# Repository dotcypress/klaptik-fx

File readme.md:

# klaptik-fx-app

## License

Licensed under either of

- Apache License, Version 2.0 ([LICENSE-APACHE](LICENSE-APACHE) or
  http://www.apache.org/licenses/LICENSE-2.0)
- MIT license ([LICENSE-MIT](LICENSE-MIT) or http://opensource.org/licenses/MIT)

at your option.

### Contribution

Unless you explicitly state otherwise, any contribution intentionally submitted
for inclusion in the work by you, as defined in the Apache-2.0 license, shall be
dual licensed as above, without any additional terms or conditions.

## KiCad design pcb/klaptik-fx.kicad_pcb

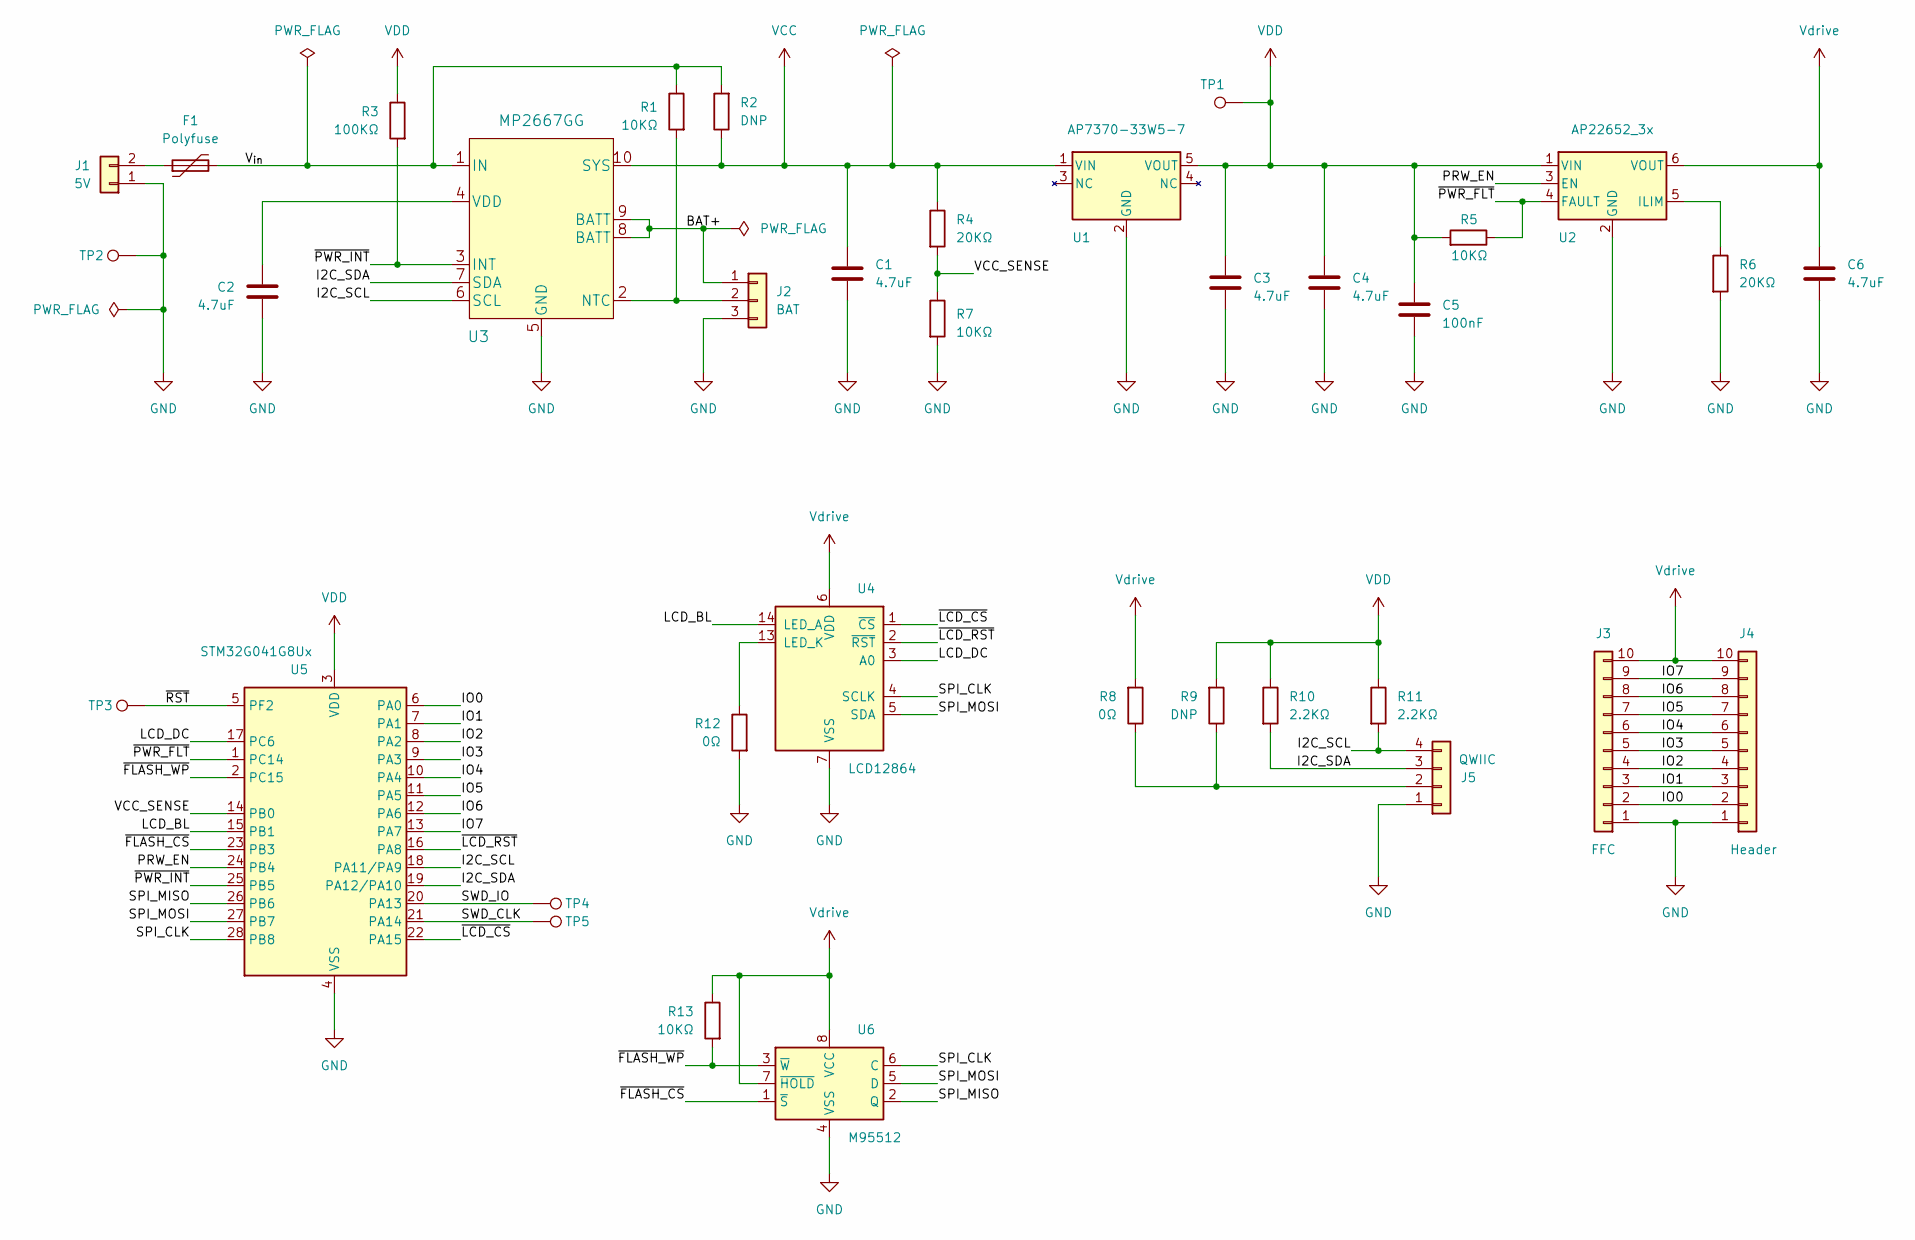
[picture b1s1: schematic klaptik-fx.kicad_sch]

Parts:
C1, C2, C3, C4, C6: 4.7uF; C_0402_1005Metric
C5: 100nF; C_0402_1005Metric
F1: Polyfuse; Fuse_0402_1005Metric
J1: 5V; PinHeader_1x02_P2.54mm_Vertical
J2: BAT; JST_SH_SM03B-SRSS-TB_1x03-1MP_P1.00mm_Horizontal
J3: FFC; Molex_54548-1071_1x10-1MP_P0.5mm_Horizontal
J4: Header; PinHeader_1x10_P1.27mm_Vertical
J5: QWIIC; JST_SH_SM04B-SRSS-TB_1x04-1MP_P1.00mm_Horizontal
R1, R5, R7, R13: 10KΩ; R_0402_1005Metric
R2, R9: DNP; R_0402_1005Metric
R3: 100KΩ; R_0402_1005Metric
R4, R6: 20KΩ; R_0402_1005Metric
R8, R12: 0Ω; R_0402_1005Metric
R10, R11: 2.2KΩ; R_0402_1005Metric
TP1: VDD; TestPoint_Pad_D1.0mm
TP2, TP3: GND; TestPoint_Pad_D1.0mm
TP4: SWD IO; TestPoint_Pad_D1.0mm
TP5: SWD CLK; TestPoint_Pad_D1.0mm
U1: AP7370-33W5-7; TSOT-23-5
U2: AP22652_3x; SOT-23-6
U3: MP2667GG; MP2667GG-xxxx-Z
U4: LCD12864; LCD_FPC_1x14_P0.80mm
U5: STM32G041G8Ux; QFN-28_4x4mm_P0.5mm
U6: M95512; TSSOP-8_4.4x3mm_P0.65mm

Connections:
/BAT+: J2.1, U3.8 (BATT), U3.9 (BATT)
/I2C_SCL: J5.4, R11.2, U3.6 (SCL), U5.18 (PA11/PA9)
/I2C_SDA: J5.3, R10.2, U3.7 (SDA), U5.19 (PA12/PA10)
/IO0: J3.2, J4.2, U5.6 (PA0)
/IO1: J3.3, J4.3, U5.7 (PA1)
/IO2: J3.4, J4.4, U5.8 (PA2)
/IO3: J3.5, J4.5, U5.9 (PA3)
/IO4: J3.6, J4.6, U5.10 (PA4)
/IO5: J3.7, J4.7, U5.11 (PA5)
/IO6: J3.8, J4.8, U5.12 (PA6)
/IO7: J3.9, J4.9, U5.13 (PA7)
/LCD_BL: U4.14 (LED_A), U5.15 (PB1)
/LCD_DC: U4.3 (A0), U5.17 (PC6)
/PRW_EN: U2.3 (EN), U5.24 (PB4)
/SPI_CLK: U4.4 (SCLK), U5.28 (PB8), U6.6 (C)
/SPI_MISO: U5.26 (PB6), U6.2 (Q)
/SPI_MOSI: U4.5 (SDA), U5.27 (PB7), U6.5 (D)
/SWD_CLK: TP5.1, U5.21 (PA14)
/SWD_IO: TP4.1, U5.20 (PA13)
/VCC_SENSE: R4.2, R7.1, U5.14 (PB0)
/V_{in}: F1.2, R1.1, R2.2, U3.1 (IN)
/~FLASH_CS: U5.23 (PB3), U6.1 (~S)
/~FLASH_WP: R13.2, U5.2 (PC15), U6.3 (~W)
/~LCD_CS: U4.1 (~CS), U5.22 (PA15)
/~LCD_RST: U4.2 (~RST), U5.16 (PA8)
/~PWR_FLT: R5.1, U2.4 (FAULT), U5.1 (PC14)
/~PWR_INT: R3.2, U3.3 (INT), U5.25 (PB5)
/~RST: TP3.1, U5.5 (PF2)
GND: C1.2, C2.2, C3.2, C4.2, C5.2, C6.2, J1.1, J2.3, J3.1, J4.1, J5.1, R6.2, R7.2, R12.2, TP2.1, U1.2 (GND), U2.2 (GND), U3.5 (GND), U4.7 (VSS), U5.4 (VSS), U6.4 (VSS)
unnamed: F1.1, J1.2
unnamed: J2.2, R1.2, U3.2 (NTC)
unnamed: J5.2, R8.1, R9.1
unnamed: R6.1, U2.5 (ILIM)
unnamed: C2.1, U3.4 (VDD)
unnamed: R12.1, U4.13 (LED_K)
VCC: C1.1, R2.1, R4.1, U1.1 (VIN), U3.10 (SYS)
VDD: C3.1, C4.1, C5.1, R3.1, R5.2, R9.2, R10.1, R11.1, TP1.1, U1.5 (VOUT), U2.1 (VIN), U5.3 (VDD)
Vdrive: C6.1, J3.10, J4.10, R8.2, R13.1, U2.6 (VOUT), U4.6 (VDD), U6.7 (~HOLD), U6.8 (VCC)

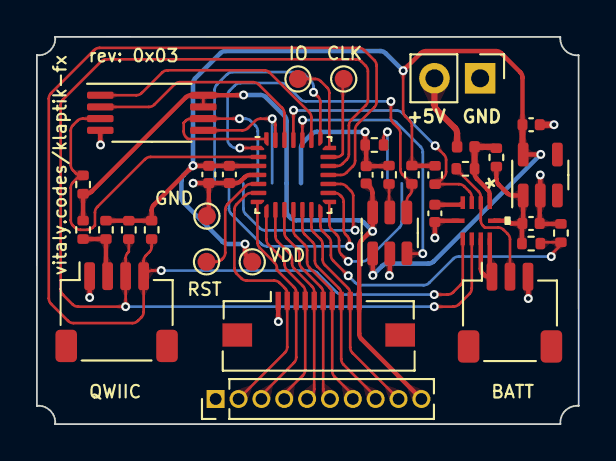
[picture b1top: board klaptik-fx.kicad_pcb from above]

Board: 4 copper layers, 30.1 x 21.5 mm, 36 parts (1 on the bottom side), 38 nets.

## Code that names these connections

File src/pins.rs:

use crate::hal::gpio::{gpioa::*, gpiob::*, gpioc::*};
use hal::gpio::*;
use hal::gpio::{DefaultMode, OpenDrain, Output, PushPull};
use hal::prelude::*;
use hal::rcc::Rcc;
use hal::stm32::*;

// SWD
pub type SwdIo = PA13<DefaultMode>;
pub type SwdClk = PA14<DefaultMode>;

// Qwiic I2C
pub type I2cClk = PA11<Output<OpenDrain>>;
pub type I2cSda = PA12<Output<OpenDrain>>;

// SPI
pub type SpiClk = PB8<DefaultMode>;
pub type SpiMiso = PB6<DefaultMode>;
pub type SpiMosi = PB7<DefaultMode>;

// Display
pub type LcdDC = PC6<Output<PushPull>>;
pub type LcdCS = PA15<Output<PushPull>>;
pub type LcdReset = PA8<Output<PushPull>>;
pub type LcdBacklight = PB1<DefaultMode>;

// EEPROM
pub type EepromCS = PB3<Output<PushPull>>;
pub type EepromWP = PC15<Output<PushPull>>;

// Power
pub type PowerEn = PB4<Output<PushPull>>;
pub type PowerInt = PB5<DefaultMode>;
pub type PowerFault = PC14<DefaultMode>;
pub type VccSense = PB0<DefaultMode>;

// GPIO
pub type Gpio0 = PA0<Input<Floating>>;
pub type Gpio1 = PA1<Input<Floating>>;
pub type Gpio2 = PA2<Input<Floating>>;
pub type Gpio3 = PA3<Input<Floating>>;
pub type Gpio4 = PA4<Input<Floating>>;
pub type Gpio5 = PA5<Input<Floating>>;
pub type Gpio6 = PA6<Input<Floating>>;
pub type Gpio7 = PA7<Input<Floating>>;

pub type I2cDev = hal::i2c::I2c<I2C2, I2cSda, I2cClk>;
pub type SpiDev = hal::spi::Spi<SPI2, (SpiClk, SpiMiso, SpiMosi)>;

pub struct Gpio {
    pub gpio0: Gpio0,
    pub gpio1: Gpio1,
    pub gpio2: Gpio2,
    pub gpio3: Gpio3,
    pub gpio4: Gpio4,
    pub gpio5: Gpio5,
    pub gpio6: Gpio6,
    pub gpio7: Gpio7,
}

pub struct Pins {
    // SWD
    pub swd_io: SwdIo,
    pub swd_clk: SwdClk,

    // Qwiic I2C
    pub i2c_clk: I2cClk,
    pub i2c_sda: I2cSda,

    // SPI
    pub spi_clk: SpiClk,
    pub spi_miso: SpiMiso,
    pub spi_mosi: SpiMosi,

    // Display
    pub lcd_dc: LcdDC,
    pub lcd_backlight: LcdBacklight,
    pub lcd_cs: LcdCS,
    pub lcd_reset: LcdReset,

    // EEPROM
    pub eeprom_cs: EepromCS,
    pub eeprom_wp: EepromWP,

    // Power
    pub power_en: PowerEn,
    pub power_int: PowerInt,
    pub power_fault: PowerFault,
    pub vcc_sense: VccSense,

    // GPIO
    pub gpio: Gpio,
}

impl Pins {
    pub fn new(gpioa: GPIOA, gpiob: GPIOB, gpioc: GPIOC, rcc: &mut Rcc) -> Self {
        let port_a = gpioa.split(rcc);
        let port_b = gpiob.split(rcc);
        let port_c = gpioc.split(rcc);

        Self {
            // SWD
            swd_io: port_a.pa13,
            swd_clk: port_a.pa14,

            // Qwiic I2C
            i2c_clk: port_a
                .pa11
                .set_speed(Speed::High)
                .into_open_drain_output_in_state(PinState::High),
            i2c_sda: port_a
                .pa12
                .set_speed(Speed::High)
                .into_open_drain_output_in_state(PinState::High),

            //SPI
            spi_clk: port_b.pb8.set_speed(Speed::VeryHigh),
            spi_miso: port_b.pb6.set_speed(Speed::VeryHigh),
            spi_mosi: port_b.pb7.set_speed(Speed::VeryHigh),

            // Display
            lcd_cs: port_a.pa15.into_push_pull_output_in_state(PinState::High),
            lcd_dc: port_c.pc6.into(),
            lcd_reset: port_a.pa8.into(),
            lcd_backlight: port_b.pb1,

            // EEPROM
            eeprom_cs: port_b.pb3.into_push_pull_output_in_state(PinState::High),
            eeprom_wp: port_c.pc15.into_push_pull_output_in_state(PinState::High),

            power_en: port_b.pb4.into(),
            power_int: port_b.pb5,
            power_fault: port_c.pc14,
            vcc_sense: port_b.pb0,

            // GPIO
            gpio: Gpio {
                gpio0: port_a.pa0.into(),
                gpio1: port_a.pa1.into(),
                gpio2: port_a.pa2.into(),
                gpio3: port_a.pa3.into(),
                gpio4: port_a.pa4.into(),
                gpio5: port_a.pa5.into(),
                gpio6: port_a.pa6.into(),
                gpio7: port_a.pa7.into(),
            },
        }
    }
}

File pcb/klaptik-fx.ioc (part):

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Mcu.Name=STM32G030F6Px
Mcu.Package=TSSOP20
Mcu.UserName=STM32G030F6Px
PA0.GPIOParameters=GPIO_Label
PA0.GPIO_Label=GPIO_1
PA0.Mode=SYS_WakeUp0
PA0.Signal=SYS_WKUP1
PA1.GPIOParameters=GPIO_Label
PA1.GPIO_Label=GPIO_2
PA1.Signal=GPIO_Input
PA11\ [PA9].GPIOParameters=GPIO_Label
PA11\ [PA9].GPIO_Label=LCD_CS
PA11\ [PA9].Signal=GPIO_Output
PA12\ [PA10].GPIOParameters=GPIO_Label
PA12\ [PA10].GPIO_Label=LCD_RESET
PA12\ [PA10].Signal=GPIO_Output
PA13.Mode=Serial_Wire
PA13.Signal=SYS_SWDIO
PA14-BOOT0.Mode=Serial_Wire
PA14-BOOT0.Signal=SYS_SWCLK
PA14-BOOT0__PA15.StandardMode=true
PA2.GPIOParameters=GPIO_Label
PA2.GPIO_Label=ENC_BTN
PA2.Signal=GPIO_Input
PA3.GPIOParameters=GPIO_Label
PA3.GPIO_Label=LCD_A0
PA3.Signal=GPIO_Output
PA4.GPIOParameters=GPIO_Label
PA4.GPIO_Label=LCD_BLK
PA4.Signal=S_TIM14_CH1
PA5.Mode=Full_Duplex_Master
PA5.Signal=SPI1_SCK
PA6.Mode=Full_Duplex_Master
PA6.Signal=SPI1_MISO
PA7.Mode=Full_Duplex_Master
PA7.Signal=SPI1_MOSI
PA8.GPIOParameters=GPIO_Label
PA8.GPIO_Label=ENC_A
PA8.Signal=S_TIM1_CH1
PB0__PB1__PB2__PA8.StandardMode=true
PB3.GPIOParameters=GPIO_Label
PB3.GPIO_Label=ENC_B
PB3.Signal=S_TIM1_CH2
PB3__PB4__PB5__PB6.StandardMode=true
PB7__PB8.StandardMode=true
PB8.Mode=I2C
PB8.Signal=I2C1_SCL
PB9.Mode=I2C
PB9.Signal=I2C1_SDA
PC14-OSC32_IN\ (PC14)__PB9.StandardMode=true
PC15-OSC32_OUT\ (PC15).GPIOParameters=GPIO_Label
PC15-OSC32_OUT\ (PC15).GPIO_Label=FLASH_CS
PC15-OSC32_OUT\ (PC15).Signal=GPIO_Output
RCC.HSE_VALUE=8000000
RCC.SYSCLKFreq_VALUE=16000000
board=custom

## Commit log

2023-01-29 stm32c0 port
2023-01-29 pcb rev 0x02
2023-01-29 ram cleanup
2023-01-30 g0 port
2023-01-30 stm32c011f6
2023-01-30 update deps
2023-02-08 add nonce
2023-02-08 c0 port
2023-02-10 update fx protocol
2023-03-16 qei feature
2023-03-16 standalone template
2023-04-23 add bom
2023-08-18 rev 0x03
2023-08-18 add drc exclusion
2023-08-25 update pinout
2023-08-27 cleanup
2023-08-27 update template
2023-09-03 update image
2023-09-05 update schematics
